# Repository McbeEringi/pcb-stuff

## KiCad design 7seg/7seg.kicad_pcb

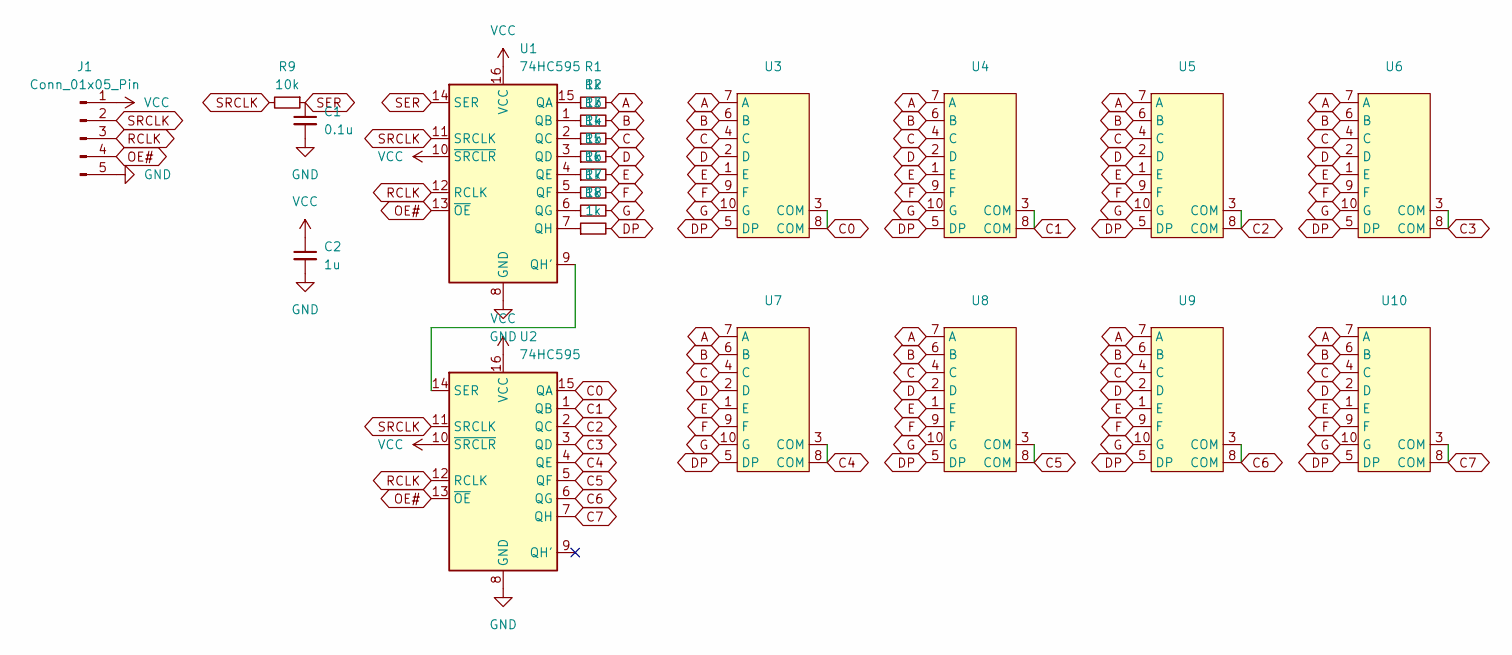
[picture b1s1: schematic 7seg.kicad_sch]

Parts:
C1: 0.1u; C_0603_1608Metric
C2: 1u; C_0603_1608Metric
J1: Conn_01x05_Pin; PinHeader_1x05_P2.54mm_Vertical
R1, R2, R3, R4, R5, R6, R7, R8: 1k; R_0603_1608Metric
R9: 10k; R_0603_1608Metric
U1, U2: 74HC595; SOP-16_4.55x10.3mm_P1.27mm
U3, U4, U5, U6, U7, U8, U9, U10: LA-501DD

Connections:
A: R1.2, U3.7 (A), U4.7 (A), U5.7 (A), U6.7 (A), U7.7 (A), U8.7 (A), U9.7 (A), U10.7 (A)
B: R2.2, U3.6 (B), U4.6 (B), U5.6 (B), U6.6 (B), U7.6 (B), U8.6 (B), U9.6 (B), U10.6 (B)
C: R3.2, U3.4 (C), U4.4 (C), U5.4 (C), U6.4 (C), U7.4 (C), U8.4 (C), U9.4 (C), U10.4 (C)
C0: U2.15 (QA), U3.3 (COM), U3.8 (COM)
C1: U2.1 (QB), U4.3 (COM), U4.8 (COM)
C2: U2.2 (QC), U5.3 (COM), U5.8 (COM)
C3: U2.3 (QD), U6.3 (COM), U6.8 (COM)
C4: U2.4 (QE), U7.3 (COM), U7.8 (COM)
C5: U2.5 (QF), U8.3 (COM), U8.8 (COM)
C6: U2.6 (QG), U9.3 (COM), U9.8 (COM)
C7: U2.7 (QH), U10.3 (COM), U10.8 (COM)
D: R4.2, U3.2 (D), U4.2 (D), U5.2 (D), U6.2 (D), U7.2 (D), U8.2 (D), U9.2 (D), U10.2 (D)
DP: R8.2, U3.5 (DP), U4.5 (DP), U5.5 (DP), U6.5 (DP), U7.5 (DP), U8.5 (DP), U9.5 (DP), U10.5 (DP)
E: R5.2, U3.1 (E), U4.1 (E), U5.1 (E), U6.1 (E), U7.1 (E), U8.1 (E), U9.1 (E), U10.1 (E)
F: R6.2, U3.9 (F), U4.9 (F), U5.9 (F), U6.9 (F), U7.9 (F), U8.9 (F), U9.9 (F), U10.9 (F)
G: R7.2, U3.10 (G), U4.10 (G), U5.10 (G), U6.10 (G), U7.10 (G), U8.10 (G), U9.10 (G), U10.10 (G)
GND: C1.2, C2.2, J1.5, U1.8 (GND), U2.8 (GND)
unnamed: R1.1, U1.15 (QA)
unnamed: R2.1, U1.1 (QB)
unnamed: R3.1, U1.2 (QC)
unnamed: R4.1, U1.3 (QD)
unnamed: R5.1, U1.4 (QE)
unnamed: R6.1, U1.5 (QF)
unnamed: R7.1, U1.6 (QG)
unnamed: U1.9 (QH'), U2.14 (SER)
unnamed: R8.1, U1.7 (QH)
OE#: J1.4, U1.13 (~OE), U2.13 (~OE)
RCLK: J1.3, U1.12 (RCLK), U2.12 (RCLK)
SER: C1.1, R9.1, U1.14 (SER)
SRCLK: J1.2, R9.2, U1.11 (SRCLK), U2.11 (SRCLK)
VCC: C2.1, J1.1, U1.10 (~SRCLR), U1.16 (VCC), U2.10 (~SRCLR), U2.16 (VCC)

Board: 2 copper layers, 22 parts (0 on the bottom side), 31 nets, no tracks yet.

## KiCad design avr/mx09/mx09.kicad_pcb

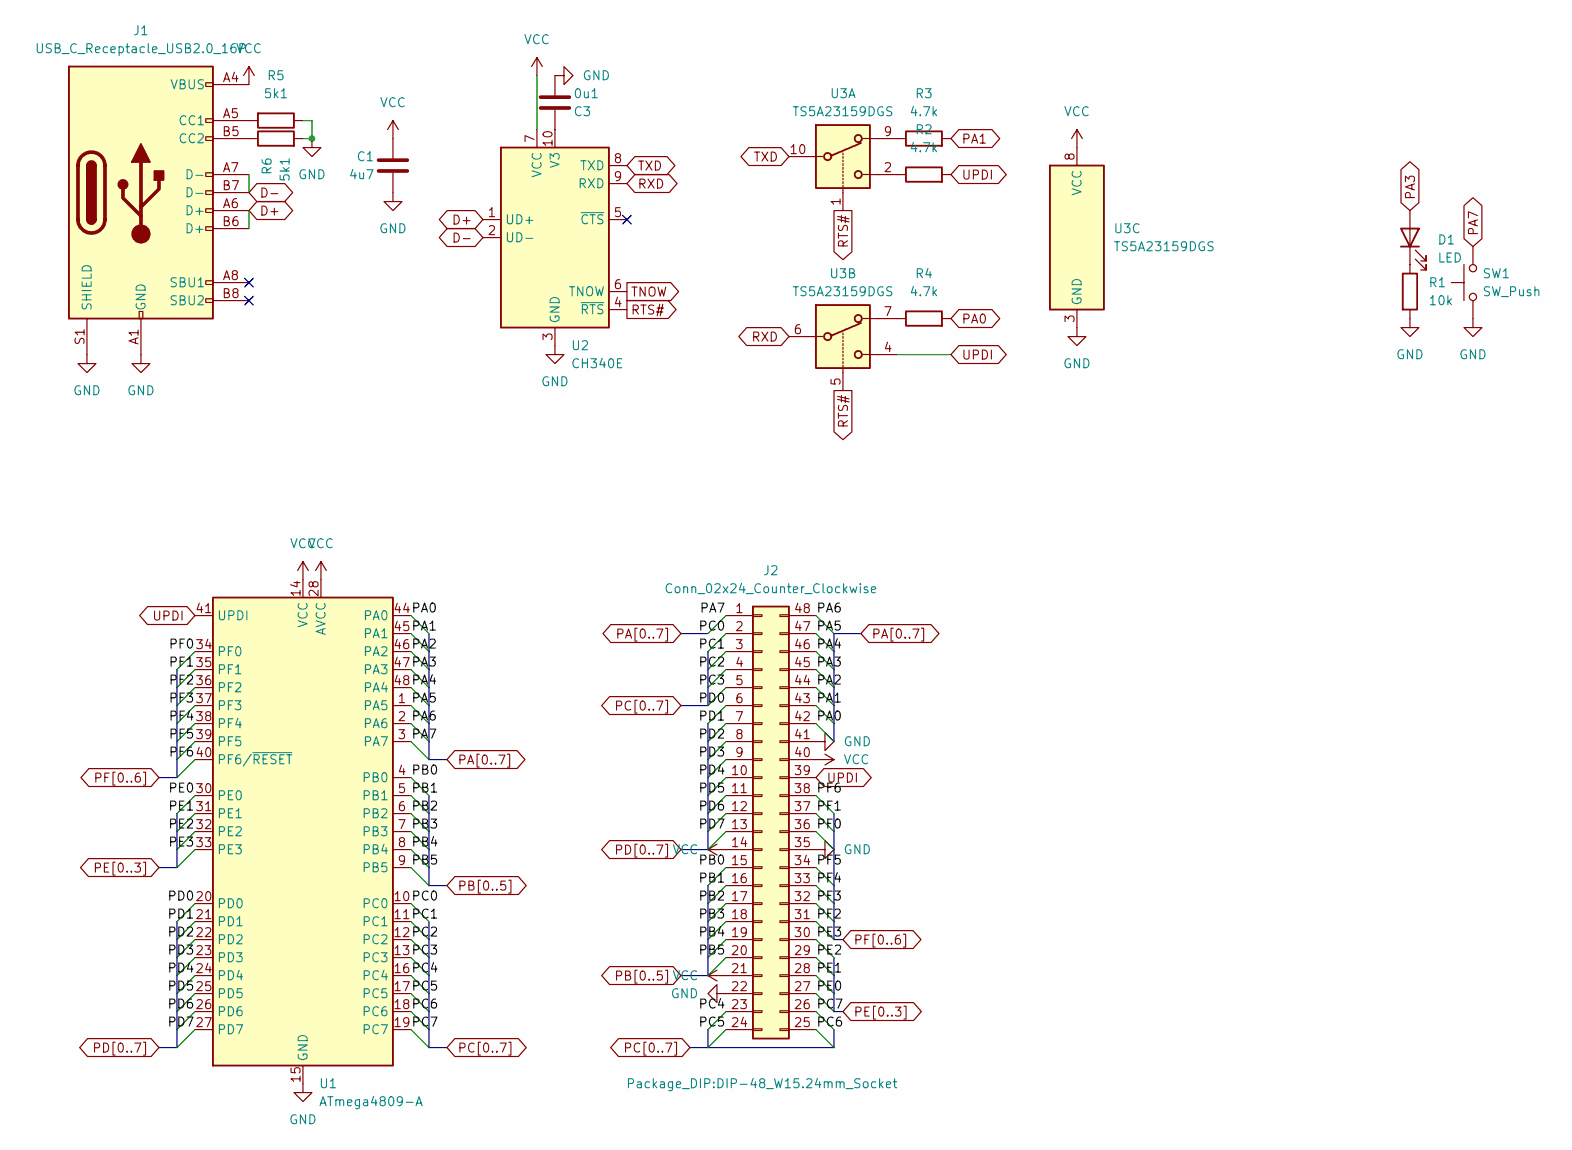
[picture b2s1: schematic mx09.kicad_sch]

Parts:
C1: 4u7; C_0603_1608Metric
C3: 0u1; C_0603_1608Metric
D1: LED; LED_0603_1608Metric
J1: USB_C_Receptacle_USB2.0_16P; USB_C_Receptacle_GCT_USB4105-xx-A_16P_TopMnt_Horizontal
J2: Conn_02x24_Counter_Clockwise; DIP-48_W15.24mm_Socket
R1: 10k; R_0603_1608Metric
R2, R3, R4: 4.7k; R_0603_1608Metric
R5, R6: 5k1; R_0603_1608Metric
SW1: SW_Push; alps-skrp
U1: ATmega4809-A; TQFP-48_7x7mm_P0.5mm
U2: CH340E; MSOP-10_3x3mm_P0.5mm
U3: TS5A23159DGS; VSSOP-10_3x3mm_P0.5mm

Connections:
D+: J1.A6 (D+), J1.B6 (D+), U2.1 (UD+)
D-: J1.A7 (D-), J1.B7 (D-), U2.2 (UD-)
GND: C1.2, C3.2, J1.A1 (GND), J1.A12 (GND), J1.B1 (GND), J1.B12 (GND), J1.S1 (SHIELD), J2.22, J2.35, J2.41, R1.2, R5.1, R6.2, SW1.1, U1.15 (GND), U1.29 (GND), U1.43 (GND), U2.3 (GND), U3.3 (GND); also elsewhere on the board
unnamed: D1.1 (K), R1.1
unnamed: J1.A5 (CC1), R5.2
unnamed: J1.B5 (CC2), R6.1
unnamed: R2.1, U3.2
unnamed: R3.1, U3.9
unnamed: R4.1, U3.7
unnamed: C3.1, U2.10 (V3)
PA0: J2.42, R4.2, U1.44 (PA0)
PA1: J2.43, R3.2, U1.45 (PA1)
PA2: J2.44, U1.46 (PA2)
PA3: D1.2 (A), J2.45, U1.47 (PA3)
PA4: J2.46, U1.48 (PA4)
PA5: J2.47, U1.1 (PA5)
PA6: J2.48, U1.2 (PA6)
PA7: J2.1, SW1.2, U1.3 (PA7)
PB0: J2.15, U1.4 (PB0)
PB1: J2.16, U1.5 (PB1)
PB2: J2.17, U1.6 (PB2)
PB3: J2.18, U1.7 (PB3)
PB4: J2.19, U1.8 (PB4)
PB5: J2.20, U1.9 (PB5)
PC0: J2.2, U1.10 (PC0)
PC1: J2.3, U1.11 (PC1)
PC2: J2.4, U1.12 (PC2)
PC3: J2.5, U1.13 (PC3)
PC4: J2.23, U1.16 (PC4)
PC5: J2.24, U1.17 (PC5)
PC6: J2.25, U1.18 (PC6)
PC7: J2.26, U1.19 (PC7)
PD0: J2.6, U1.20 (PD0)
PD1: J2.7, U1.21 (PD1)
PD2: J2.8, U1.22 (PD2)
PD3: J2.9, U1.23 (PD3)
PD4: J2.10, U1.24 (PD4)
PD5: J2.11, U1.25 (PD5)
PD6: J2.12, U1.26 (PD6)
PD7: J2.13, U1.27 (PD7)
PE0: J2.27, U1.30 (PE0)
PE1: J2.28, U1.31 (PE1)
PE2: J2.29, U1.32 (PE2)
PE3: J2.30, U1.33 (PE3)
PF0: J2.36, U1.34 (PF0)
PF1: J2.37, U1.35 (PF1)
PF2: J2.31, U1.36 (PF2)
PF3: J2.32, U1.37 (PF3)
PF4: J2.33, U1.38 (PF4)
PF5: J2.34, U1.39 (PF5)
PF6: J2.38, U1.40 (PF6/~RESET)
RTS#: U2.4 (~RTS), U3.1, U3.5
RXD: U2.9 (RXD), U3.6
TNOW: U2.6 (TNOW); also elsewhere on the board
TXD: U2.8 (TXD), U3.10
UPDI: J2.39, R2.2, U1.41 (UPDI), U3.4
VCC: C1.1, J1.A4 (VBUS), J1.A9 (VBUS), J1.B4 (VBUS), J1.B9 (VBUS), J2.14, J2.21, J2.40, U1.14 (VCC), U1.28 (AVCC), U1.42 (VCC), U2.7 (VCC), U3.8 (VCC)

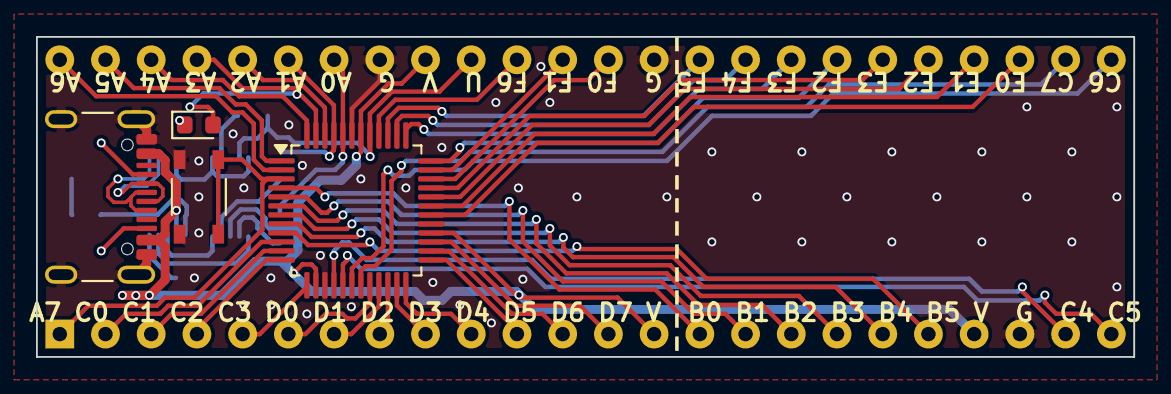
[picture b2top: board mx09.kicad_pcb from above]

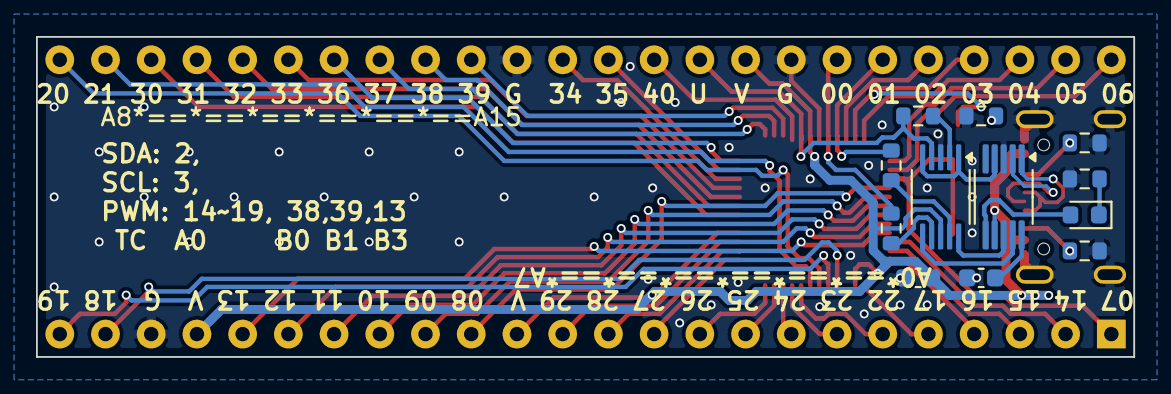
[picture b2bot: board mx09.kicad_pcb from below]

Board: 2 copper layers, 61.0 x 17.8 mm, 17 parts (12 on the bottom side), 58 nets.

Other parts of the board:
D2: LED; LED_0603_1608Metric
R7: 10k; R_0603_1608Metric

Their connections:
GND: R7.2; also elsewhere on the board
unnamed: D2.1 (K), R7.1
TNOW: D2.2 (A); also elsewhere on the board

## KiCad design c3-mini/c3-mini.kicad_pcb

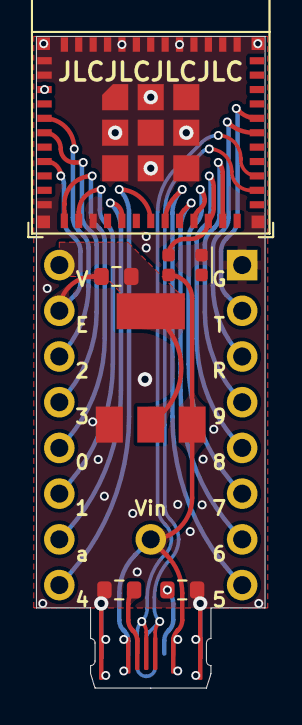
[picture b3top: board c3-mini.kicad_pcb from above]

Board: 2 copper layers, 12.7 x 36.2 mm, 10 parts (0 on the bottom side), 21 nets.

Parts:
J1: USB-C
J2, J4: Conn_01x08_Pin; PinHeader_1x08_P2.54mm_Vertical
J3: Conn_01x01_Pin; PinHeader_1x01_P2.54mm_Vertical
R1: 10k; R_0603_1608Metric
R2, R3: 5.1k; R_0603_1608Metric
U2: LM1117MP-3.3; SOT-223-3_TabPin2
U3: WS2812C; WS2812C-2020
U4: ESP32-C3-MINI-1

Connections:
+3.3V: J2.1, R1.1, U2.2 (VO), U4.3 (3V3)
+5V: J1.4 (VBUS), J3.1, U2.3 (VI), U3.4 (VDD)
D+: J1.2 (D+), U4.27 (GPIO19/USB_D+)
D-: J1.3 (D-), U4.26 (GPIO18/USB_D-)
EN: J2.2, R1.2, U4.8 (EN/CHIP_PU)
GND: J1.1 (GND), J4.1, R2.2, R3.2, U2.1 (GND), U3.2 (GND), U4.1 (GND), U4.2 (GND), U4.11 (GND), U4.14 (GND), U4.36 (GND), U4.37 (GND), U4.38 (GND), U4.39 (GND), U4.40 (GND), U4.41 (GND), U4.42 (GND), U4.43 (GND), U4.44 (GND), U4.45 (GND), U4.46 (GND), U4.47 (GND), U4.48 (GND), U4.49 (GND), U4.50 (GND), U4.51 (GND), U4.52 (GND), U4.53 (GND)
IO0: J2.5, U4.12 (GPIO0/ADC1_CH0/XTAL_32K_P)
IO1: J2.6, U4.13 (GPIO1/ADC1_CH1/XTAL_32K_N)
IO2: J2.3, U4.5 (GPIO2/ADC1_CH2)
IO3: J2.4, U4.6 (GPIO3/ADC1_CH3)
IO4: J2.8, U4.18 (GPIO4/ADC1_CH4)
IO5: J4.8, U4.19 (GPIO5/ADC2_CH0)
IO6: J4.7, U4.20 (GPIO6)
IO7: J4.6, U4.21 (GPIO7)
IO8: J4.5, U3.3 (DI), U4.22 (GPIO8)
IO9: J4.4, U4.23 (GPIO9)
IO10: J2.7, U4.16 (GPIO10)
unnamed: J1.5 (CC1), R3.1
unnamed: J1.6 (CC2), R2.1
RXD: J4.3, U4.30 (GPIO20/U0RXD)
TXD: J4.2, U4.31 (GPIO21/U0TXD)
